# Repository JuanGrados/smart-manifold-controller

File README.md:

# smart-manifold-controller

__Documentation in progress....__

This is a repository for a smart manifold controller.
It is a porject to control 4 electric water valves and measure the water flow of each of them with water flow sensors.

The project is build around the ESP32-C3-Mini and it is programmed using ESPHome.

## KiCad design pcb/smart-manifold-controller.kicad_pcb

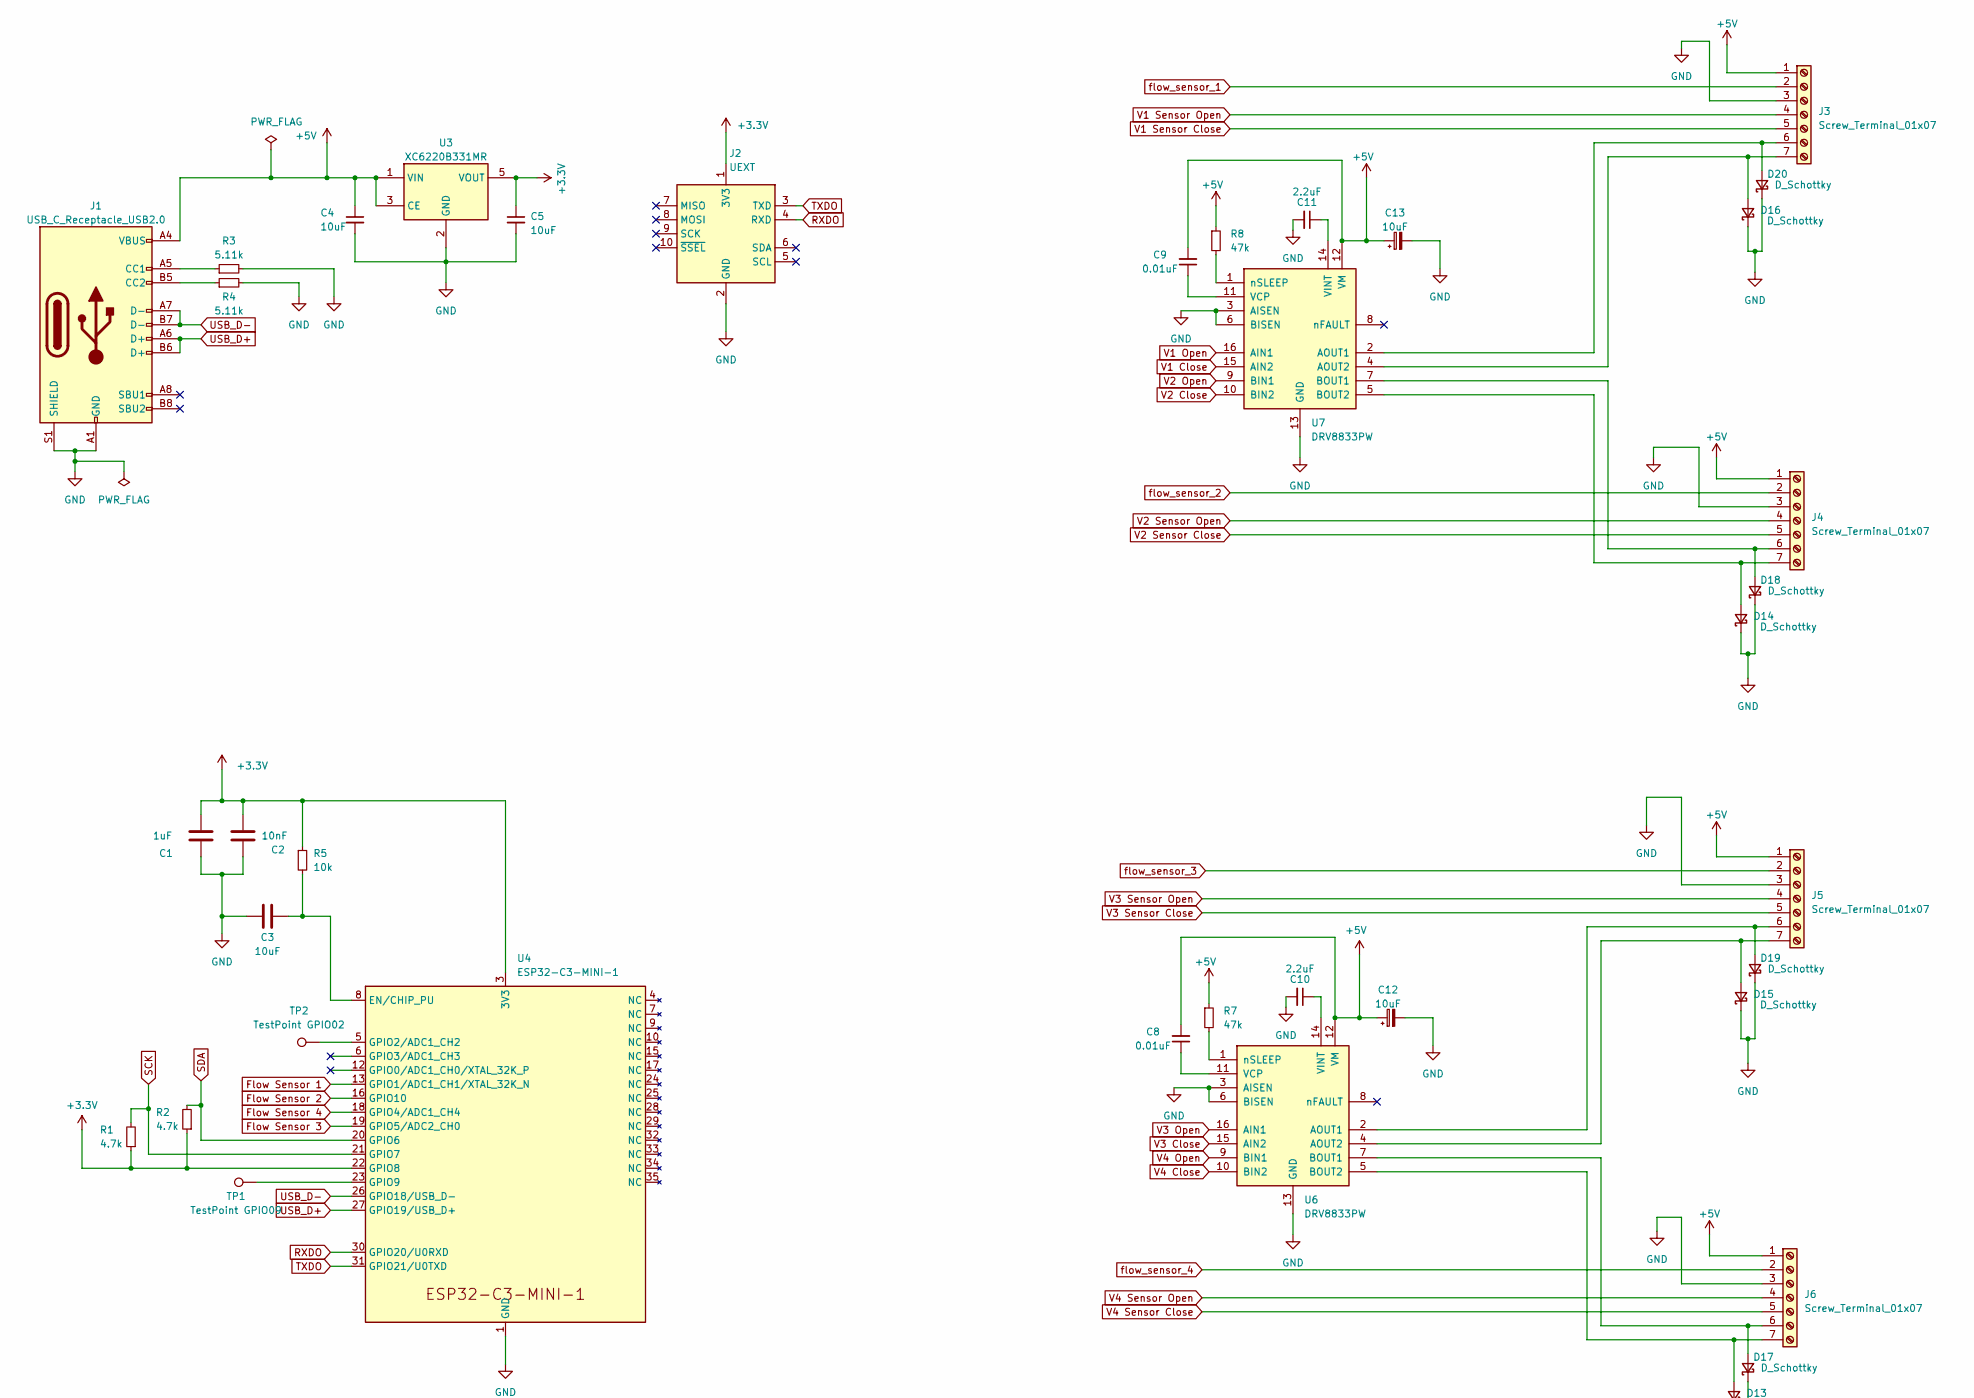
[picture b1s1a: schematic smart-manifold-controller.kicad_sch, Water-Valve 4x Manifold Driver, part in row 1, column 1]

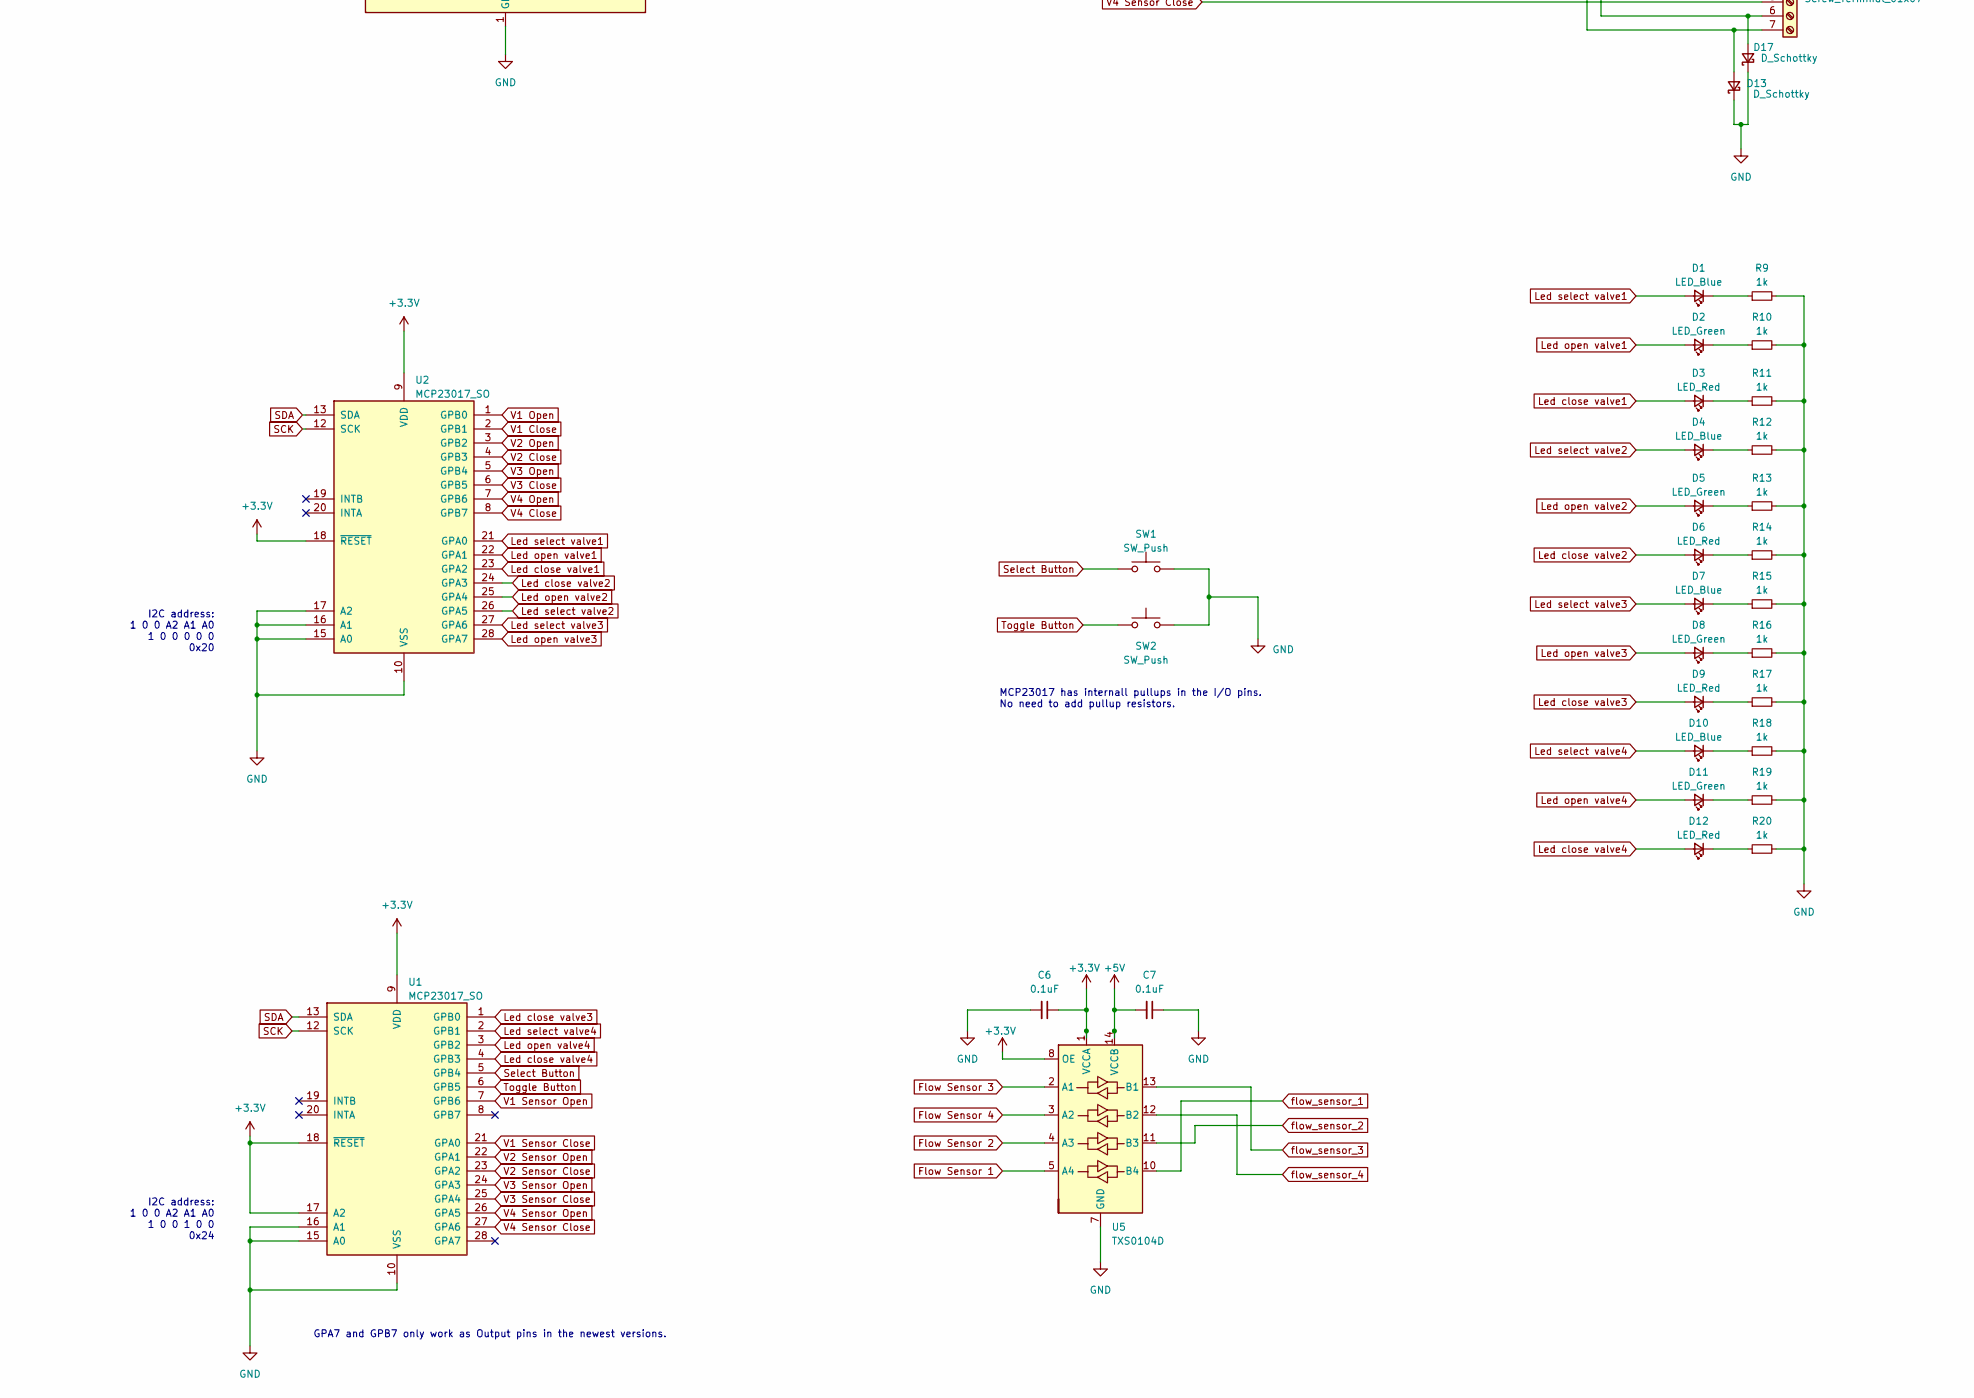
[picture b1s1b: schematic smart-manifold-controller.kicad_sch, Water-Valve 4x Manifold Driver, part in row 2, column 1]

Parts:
C1: 1uF; C_0603_1608Metric
C2: 10nF; C_0603_1608Metric
C3, C4, C5, C12, C13: 10uF; C_0603_1608Metric
C6, C7: 0.1uF; C_0603_1608Metric
C8, C9: 0.01uF; C_0603_1608Metric
C10, C11: 2.2uF; C_0603_1608Metric
D1, D4, D7, D10: LED_Blue; LED_1206_3216Metric
D2, D5, D8, D11: LED_Green; LED_1206_3216Metric
D3, D6, D9, D12: LED_Red; LED_1206_3216Metric
D13, D14, D15, D16, D17, D18, D19, D20: D_Schottky; D_0603_1608Metric
J1: USB_C_Receptacle_USB2.0; USB_C_Receptacle_HRO_TYPE-C-31-M-12
J2: UEXT; JST_EH_S4B-EH_1x04_P2.50mm_Horizontal
J3, J4, J5, J6: Screw_Terminal_01x07; TerminalBlock_Phoenix_MKDS-1,5-7-5.08_1x07_P5.08mm_Horizont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
R1, R2: 4.7k; R_0603_1608Metric
R3, R4: 5.11k; R_0603_1608Metric
R5: 10k; R_0603_1608Metric
R7, R8: 47k; R_0603_1608Metric
R9, R10, R11, R12, R13, R14, R15, R16, R17, R18, R19, R20: 1k; R_0603_1608Metric
SW1, SW2: SW_Push; SW_Push_1P1T_NO_6x6mm_H9.5mm
TP1: TestPoint GPIO09; TestPoint_Pad_D2.0mm
TP2: TestPoint GPIO02; TestPoint_Pad_D2.0mm
U1, U2: MCP23017_SO; SOIC-28W_7.5x17.9mm_P1.27mm
U3: XC6220B331MR; SOT-23-5
U4: ESP32-C3-MINI-1
U5: TXS0104D; SOIC-14_3.9x8.7mm_P1.27mm
U6, U7: DRV8833PW; TSSOP-16_4.4x5mm_P0.65mm

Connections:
+3.3V: C1.1, C2.1, C5.1, C6.1, J2.1 (3V3), R1.1, R2.1, R5.1, U1.9 (VDD), U1.17 (A2), U1.18 (~RESET), U2.9 (VDD), U2.18 (~RESET), U3.5 (VOUT), U4.3 (3V3), U4.22 (GPIO8), U5.1 (VCCA), U5.8 (OE)
+5V: C4.1, C7.2, C8.2, C9.2, C12.1, C13.1, J1.A4 (VBUS), J1.A9 (VBUS), J1.B4 (VBUS), J1.B9 (VBUS), J3.1, J4.1, J5.1, J6.1, R7.1, R8.1, U3.1 (VIN), U3.3 (CE), U5.14 (VCCB), U6.12 (VM), U7.12 (VM)
Flow Sensor 1: U4.13 (GPIO1/ADC1_CH1/XTAL_32K_N), U5.5 (A4)
Flow Sensor 2: U4.16 (GPIO10), U5.4 (A3)
Flow Sensor 3: U4.19 (GPIO5/ADC2_CH0), U5.2 (A1)
Flow Sensor 4: U4.18 (GPIO4/ADC1_CH4), U5.3 (A2)
GND: C1.2, C2.2, C3.1, C4.2, C5.2, C6.2, C7.1, C10.2, C11.2, C12.2, C13.2, D13.1 (K), D14.1 (K), D15.1 (K), D16.1 (K), D17.1 (K), D18.1 (K), D19.1 (K), D20.1 (K), J1.A1 (GND), J1.A12 (GND), J1.B1 (GND), J1.B12 (GND), J1.S1 (SHIELD), J2.2 (GND), J3.3, J4.3, J5.3, J6.3, R3.2, R4.2, R9.2, R10.2, R11.2, R12.2, R13.2, R14.2, R15.2, R16.2, R17.2, R18.2, R19.2, R20.2, SW1.2, SW2.2, U1.10 (VSS), U1.15 (A0), U1.16 (A1), U2.10 (VSS), U2.15 (A0), U2.16 (A1), U2.17 (A2), U3.2 (GND), U4.1 (GND), U4.2 (GND), U4.11 (GND), U4.14 (GND), U4.36 (GND), U4.37 (GND), U4.38 (GND), U4.39 (GND), U4.40 (GND), U4.41 (GND), U4.42 (GND), U4.43 (GND), U4.44 (GND), U4.45 (GND), U4.46 (GND), U4.47 (GND), U4.48 (GND), U4.49 (GND), U4.50 (GND), U4.51 (GND), U4.52 (GND), U4.53 (GND), U5.7 (GND), U6.3 (AISEN), U6.6 (BISEN), U6.13 (GND), U7.3 (AISEN), U7.6 (BISEN), U7.13 (GND)
Led close valve1: D3.2 (A), U2.23 (GPA2)
Led close valve2: D6.2 (A), U2.24 (GPA3)
Led close valve3: D9.2 (A), U1.1 (GPB0)
Led close valve4: D12.2 (A), U1.4 (GPB3)
Led open valve1: D2.2 (A), U2.22 (GPA1)
Led open valve2: D5.2 (A), U2.25 (GPA4)
Led open valve3: D8.2 (A), U2.28 (GPA7)
Led open valve4: D11.2 (A), U1.3 (GPB2)
Led select valve1: D1.2 (A), U2.21 (GPA0)
Led select valve2: D4.2 (A), U2.26 (GPA5)
Led select valve3: D7.2 (A), U2.27 (GPA6)
Led select valve4: D10.2 (A), U1.2 (GPB1)
unnamed: D1.1 (K), R9.1
unnamed: D2.1 (K), R10.1
unnamed: D3.1 (K), R11.1
unnamed: D4.1 (K), R12.1
unnamed: D5.1 (K), R13.1
unnamed: D6.1 (K), R14.1
unnamed: D7.1 (K), R15.1
unnamed: D8.1 (K), R16.1
unnamed: D9.1 (K), R17.1
unnamed: D10.1 (K), R18.1
unnamed: D11.1 (K), R19.1
unnamed: D12.1 (K), R20.1
unnamed: D13.2 (A), J6.7, U6.5 (BOUT2)
unnamed: D14.2 (A), J4.7, U7.5 (BOUT2)
unnamed: D15.2 (A), J5.7, U6.4 (AOUT2)
unnamed: D16.2 (A), J3.7, U7.4 (AOUT2)
unnamed: D17.2 (A), J6.6, U6.7 (BOUT1)
unnamed: D18.2 (A), J4.6, U7.7 (BOUT1)
unnamed: D19.2 (A), J5.6, U6.2 (AOUT1)
unnamed: D20.2 (A), J3.6, U7.2 (AOUT1)
unnamed: J1.A5 (CC1), R3.1
unnamed: J1.B5 (CC2), R4.1
unnamed: C3.2, R5.2, U4.8 (EN/CHIP_PU)
unnamed: TP2.1, U4.5 (GPIO2/ADC1_CH2)
unnamed: TP1.1, U4.23 (GPIO9)
unnamed: C8.1, U6.11 (VCP)
unnamed: C10.1, U6.14 (VINT)
unnamed: R7.2, U6.1 (nSLEEP)
unnamed: C9.1, U7.11 (VCP)
unnamed: C11.1, U7.14 (VINT)
unnamed: R8.2, U7.1 (nSLEEP)
RXDO: J2.4 (RXD), U4.30 (GPIO20/U0RXD)
SCK: R1.2, U1.12 (SCK), U2.12 (SCK), U4.21 (GPIO7)
SDA: R2.2, U1.13 (SDA), U2.13 (SDA), U4.20 (GPIO6)
Select Button: SW1.1, U1.5 (GPB4)
TXDO: J2.3 (TXD), U4.31 (GPIO21/U0TXD)
Toggle Button: SW2.1, U1.6 (GPB5)
USB_D+: J1.A6 (D+), J1.B6 (D+), U4.27 (GPIO19/USB_D+)
USB_D-: J1.A7 (D-), J1.B7 (D-), U4.26 (GPIO18/USB_D-)
V1 Close: U2.2 (GPB1), U7.15 (AIN2)
V1 Open: U2.1 (GPB0), U7.16 (AIN1)
V1 Sensor Close: J3.5, U1.21 (GPA0)
V1 Sensor Open: J3.4, U1.7 (GPB6)
V2 Close: U2.4 (GPB3), U7.10 (BIN2)
V2 Open: U2.3 (GPB2), U7.9 (BIN1)
V2 Sensor Close: J4.5, U1.23 (GPA2)
V2 Sensor Open: J4.4, U1.22 (GPA1)
V3 Close: U2.6 (GPB5), U6.15 (AIN2)
V3 Open: U2.5 (GPB4), U6.16 (AIN1)
V3 Sensor Close: J5.5, U1.25 (GPA4)
V3 Sensor Open: J5.4, U1.24 (GPA3)
V4 Close: U2.8 (GPB7), U6.10 (BIN2)
V4 Open: U2.7 (GPB6), U6.9 (BIN1)
V4 Sensor Close: J6.5, U1.27 (GPA6)
V4 Sensor Open: J6.4, U1.26 (GPA5)
flow_sensor_1: J3.2, U5.10 (B4)
flow_sensor_2: J4.2, U5.11 (B3)
flow_sensor_3: J5.2, U5.13 (B1)
flow_sensor_4: J6.2, U5.12 (B2)

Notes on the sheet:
GPA7 and GPB7 only work as Output pins in the newest versions.
I2C address: 1 0 0 A2 A1 A0 1 0 0 0 0 0 0x20
I2C address: 1 0 0 A2 A1 A0 1 0 0 1 0 0 0x24
MCP23017 has internall pullups in the I/O pins. No need to add pullup resistors.

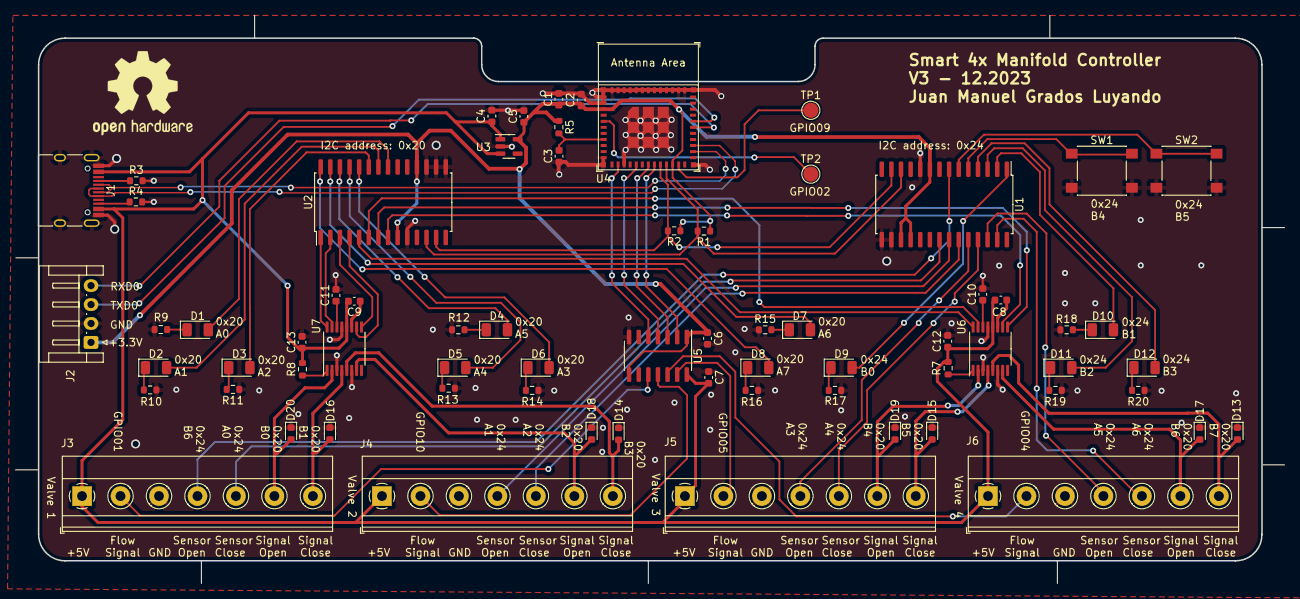
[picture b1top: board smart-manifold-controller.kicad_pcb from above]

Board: 2 copper layers, 167.6 x 75.0 mm, 69 parts (0 on the bottom side), 78 nets.

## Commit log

2024-11-07 Add files via upload
    PCB files
2024-11-07 Add files via upload
    esphome firmware
2024-11-07 Update README.md
    Some info in Readme
